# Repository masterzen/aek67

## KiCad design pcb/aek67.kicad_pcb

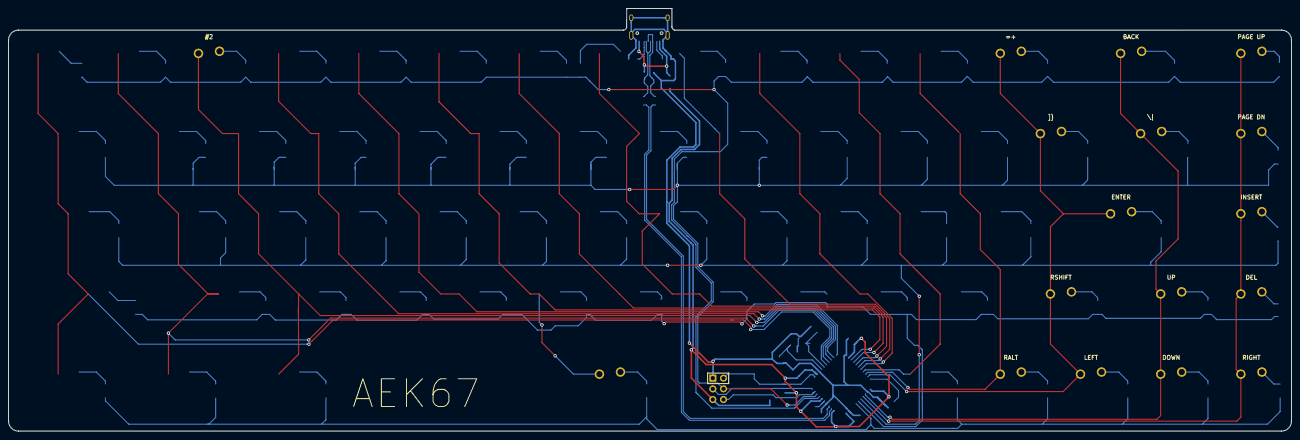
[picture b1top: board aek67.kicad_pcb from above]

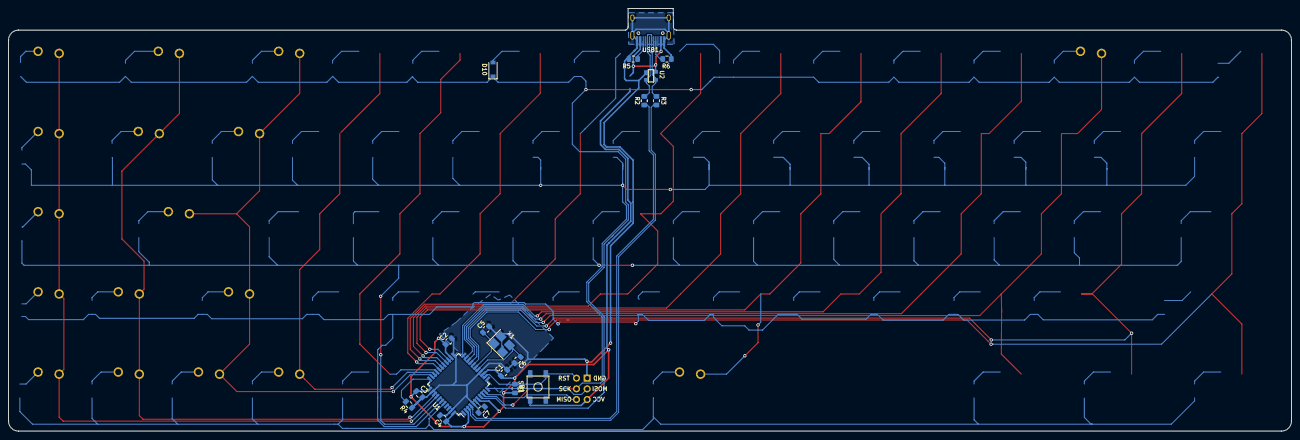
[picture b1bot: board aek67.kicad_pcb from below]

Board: 2 copper layers, 304.8 x 100.4 mm, 38 parts (19 on the bottom side), 24 nets.

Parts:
C1, C2, C3: 0.1u; C_0805_2012Metric_Pad1.15x1.40mm_HandSolder
C4: 10u; C_0805_2012Metric_Pad1.15x1.40mm_HandSolder
C5, C6: 22p; C_0805_2012Metric_Pad1.15x1.40mm_HandSolder
C7: 1u; C_0805_2012Metric_Pad1.15x1.40mm_HandSolder
D10: D_9; D_SOD-123
J1: AVR-ISP-6; Reset_Pretty-Mask
K3: #2; ALPS-1U
K13: =+; ALPS-1U
K14: BACK; ALPS-2U
K15: PAGE UP; ALPS-1U
K28: ]}; ALPS-1U
K29: \|; ALPS-1.5U
K30: PAGE DN; ALPS-1U
K42: '; ALPS-1U
K43: ENTER; ALPS-2.25U
K44: INSERT; ALPS-1U
K56: RSHIFT; ALPS-1.75U
K57: UP; ALPS-1U
K58: DEL; ALPS-1U
K62: SPACE; ALPS-6.5U
K64: RALT; ALPS-1U
K65: LEFT; ALPS-1U
K66: DOWN; ALPS-1U
K67: RIGHT; ALPS-1U
R1, R4: 10k; R_0805_2012Metric_Pad1.15x1.40mm_HandSolder
R2, R3: 22; R_0805_2012Metric_Pad1.15x1.40mm_HandSolder
R5, R6: 5.1k; R_0805_2012Metric_Pad1.15x1.40mm_HandSolder
SW1: SW_PUSH; SKQG-1155865
U1: ATmega32U4-AU; TQFP-44_10x10mm_P0.8mm
U2: PRTR5V0U2X; SOT143B
USB1: HRO-TYPE-C-31-M-12; HRO-TYPE-C-31-M-12-HandSoldering
X1: XTAL_GND; Crystal_SMD_3225-4Pin_3.2x2.5mm_HandSoldering

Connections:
+5V: C1.1, C2.1, C3.1, C4.1, J1.2, R1.2, SW1.1, U1.2, U1.7, U1.14, U1.24, U1.34, U1.44
D+: R2.2, U2.2, USB1.6, USB1.8
D-: R3.2, U2.3, USB1.5, USB1.7
GND: C1.2, C2.2, C3.2, C4.2, C5.2, C6.2, C7.2, J1.6, R4.1, R5.1, R6.2, U1.5, U1.15, U1.23, U1.35, U1.43, U2.1, USB1.1, USB1.12, USB1.13, X1.2, X1.4
MISO: J1.1, U1.10
MOSI: J1.4, U1.11
unnamed: C7.1, U1.6
unnamed: R2.1, U1.4
unnamed: R3.1, U1.3
unnamed: R4.2, U1.33
unnamed: R5.2, USB1.10
unnamed: R6.1, USB1.4
RST: J1.5, R1.1, SW1.2, U1.13
SCLK: J1.3, U1.9
VCC: U2.4, USB1.2, USB1.11
XTAL1: C5.1, U1.17, X1.1
XTAL2: C6.1, U1.16, X1.3
col2: K3.1, U1.20
col5: K62.1, U1.25
col11: K64.1, U1.31
col12: K13.1, K28.1, K43.1, K56.1, K65.1, U1.32
col13: K14.1, K29.1, K57.1, K66.1, U1.36
col14: K15.1, K30.1, K44.1, K58.1, K67.1, U1.37
row0: D10.1, U1.8

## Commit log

2019-12-28 initial version of AEK67
2019-12-28 finished MCU schematics
2019-12-28 Added matrix and footprints
2019-12-29 All switches & diodes in place
2019-12-29 USB connector & cut lines
2019-12-29 Forgot cristal GND
2019-12-29 position all elements inside PCB
2019-12-29 Fix GND that wasn't really a GND
2019-12-30 routed switches vertical & diodes
2019-12-30 row0
2019-12-30 re-annotated everything in line instead of column
    which is more clear for the matrix
2019-12-30 row1
2019-12-30 row2
2019-12-30 row3
2019-12-30 reorder rows/cols to MCU pins
    to better orient them
2019-12-30 routed rows
2019-12-30 routed almost all rows& columns
2019-12-30 all signals connected
2019-12-30 routed GND to MCU
2019-12-30 routed +5V
2019-12-30 remove row0 multiple tracks
2019-12-30 fixes some invisible tracks remains
2019-12-30 added a GND zone around the oscillator
2019-12-30 add GND zone below MCU
2019-12-30 Added copyright
2019-12-30 added mesurement
2019-12-30 Adding Gerber files
2019-12-31 Fix footprints of Capacitors
2019-12-31 fix footprint of backslash
2019-12-31 update capacitor footprints
2019-12-31 use the correct crystal footprints
    with opposite XTAL pads, in consequence redid the GND zones
2019-12-31 rerouted USB D+/D- signal for EMI protection
    far from other signals
2019-12-31 renamed key values for silks layer
2019-12-31 updated key text on front silks side
2019-12-31 latest production gerber files
2019-12-31 turns out it 22ohm, not 22k for D+/D-
2019-12-31 redesigned row2
    to prevent acute angles
2020-01-01 Fixed capacitor placement around MCU
    and rerouted GND/Vcc to the MCU
2020-01-01 re-designed row0

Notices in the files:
pcb/aek67.kicad_pcb:
© 2019 masterzen
